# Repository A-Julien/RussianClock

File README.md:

# Projet Réveil Russe

## Présentation

Le réveil russe est une invention géniale de tube électronique pour un affichage 7 segments extremment classieux.

L'effet rendu est très geek vintage.

Nous avons l'objectif de créer une horloge à partir de ce type de tube, drivé astucieusement par un composant MAX et controllé en python par une carte Raspberry Pi 3.

## Développement

Nous allons développer le mappage des composants ainsi que le programme de controle du MAX en python.

## Documentation

Nous allons utiliser un certain nombre de documents, que nous poserons dans le dossier Documentation.

## Auteurs

Nous sommes étudiants en IUT d'informatique et à Polytech.

+	Julien Alaimo
+	Nans Faudon
+	Raphaël Castanier

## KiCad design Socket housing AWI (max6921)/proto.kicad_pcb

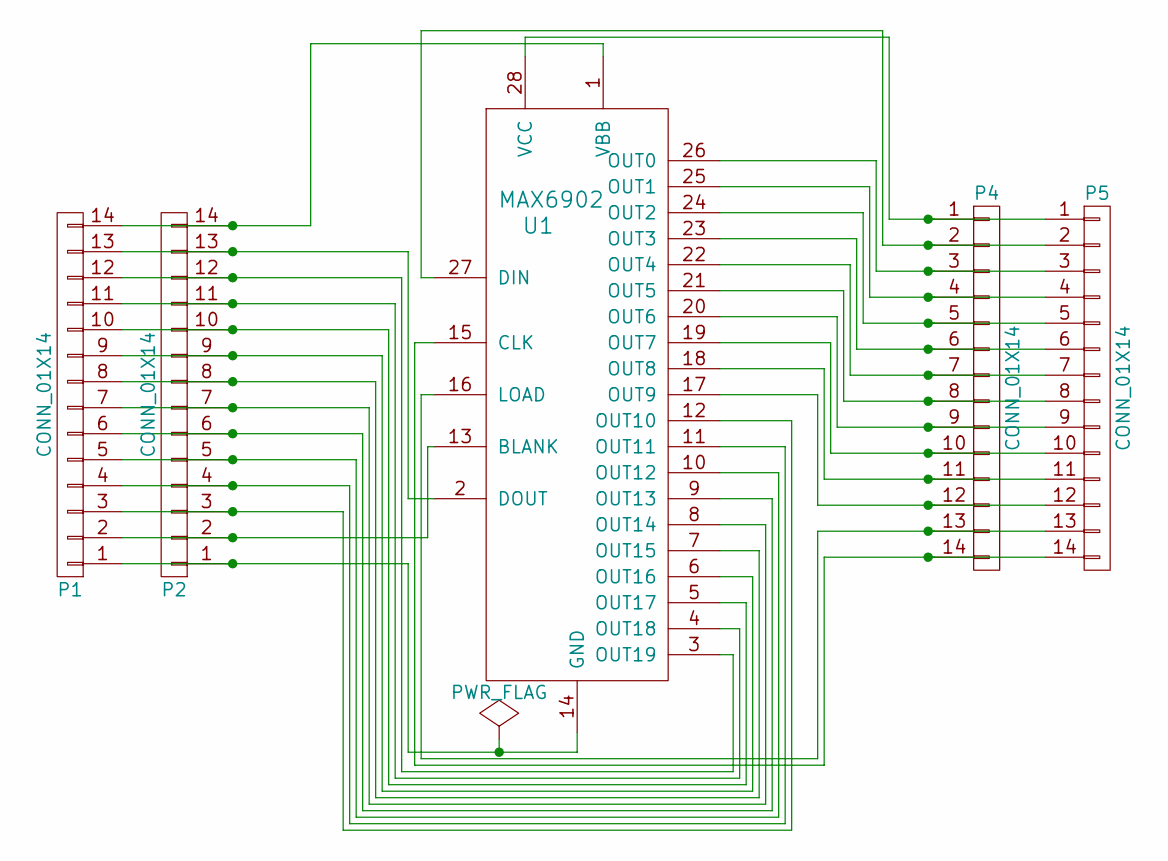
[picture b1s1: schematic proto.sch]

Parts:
P1, P2, P4, P5: CONN_01X14; Pin_Header_Straight_1x14_Pitch2.54mm
U1: MAX6902; MAX6921 - SOP28

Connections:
unnamed: P1.1, P2.1, U1.14 (GND)
unnamed: P1.2, P2.2, U1.13 (BLANK)
unnamed: P1.3, P2.3, U1.12 (OUT10)
unnamed: P1.4, P2.4, U1.11 (OUT11)
unnamed: P1.5, P2.5, U1.10 (OUT12)
unnamed: P1.6, P2.6, U1.9 (OUT13)
unnamed: P1.7, P2.7, U1.8 (OUT14)
unnamed: P1.8, P2.8, U1.7 (OUT15)
unnamed: P1.9, P2.9, U1.6 (OUT16)
unnamed: P1.10, P2.10, U1.5 (OUT17)
unnamed: P1.11, P2.11, U1.4 (OUT18)
unnamed: P1.12, P2.12, U1.3 (OUT19)
unnamed: P1.13, P2.13, U1.2 (DOUT)
unnamed: P1.14, P2.14, U1.1 (VBB)
unnamed: P4.1, P5.1, U1.28 (VCC)
unnamed: P4.2, P5.2, U1.27 (DIN)
unnamed: P4.3, P5.3, U1.26 (OUT0)
unnamed: P4.4, P5.4, U1.25 (OUT1)
unnamed: P4.5, P5.5, U1.24 (OUT2)
unnamed: P4.6, P5.6, U1.23 (OUT3)
unnamed: P4.7, P5.7, U1.22 (OUT4)
unnamed: P4.8, P5.8, U1.21 (OUT5)
unnamed: P4.9, P5.9, U1.20 (OUT6)
unnamed: P4.10, P5.10, U1.19 (OUT7)
unnamed: P4.11, P5.11, U1.18 (OUT8)
unnamed: P4.12, P5.12, U1.17 (OUT9)
unnamed: P4.13, P5.13, U1.16 (LOAD)
unnamed: P4.14, P5.14, U1.15 (CLK)

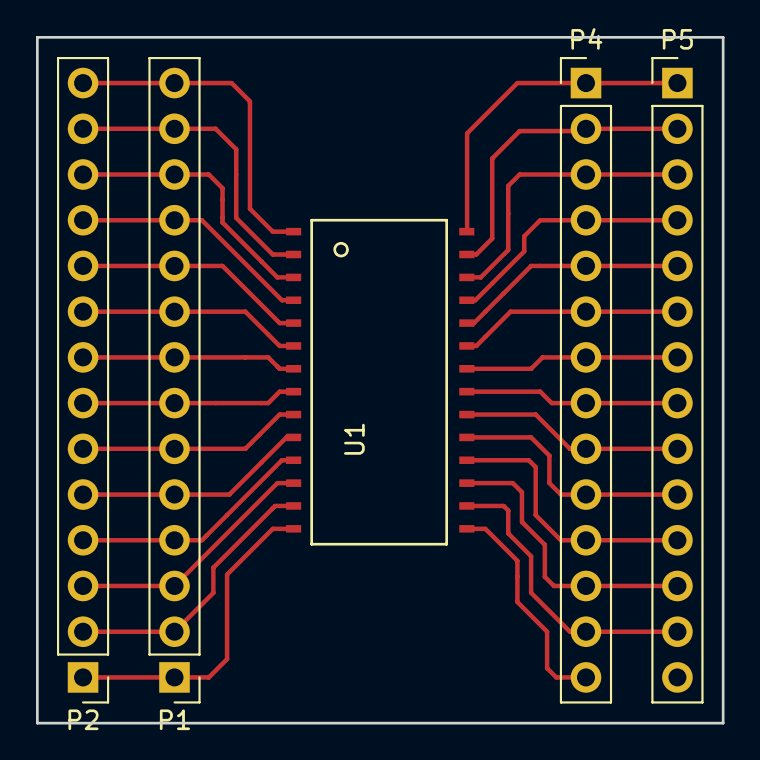
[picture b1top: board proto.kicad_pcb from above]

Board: 2 copper layers, 38.1 x 38.1 mm, 5 parts (0 on the bottom side), 28 nets.

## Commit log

2017-01-26 test de git
2017-01-26 Ajout de Coucou.md
2017-01-26 caonnard
2017-01-26 test mes couilles
2017-01-26 test encore
2017-01-26 Ajout des premiers srcipts python
2017-01-26 test commit branch
2017-01-26 bouffon
2017-01-26 supression de Coucou.md
2017-01-26 Change README.md
2017-01-26 Ajout de la doc du driver VFD
2017-01-26 Documentation
2017-01-26 Remove doc : creation d'un fichier dedié
2017-01-26 Ajout doc
2017-01-26 Rédaction de la présentation du README
2017-01-26 Mise à jour de la documentation
2017-02-05 ajout de la carte Socket pour le MAX6921 (CMS to Traversant)
2017-02-08 Ajout de fonctions de test pour le MAX
2017-03-12 Fix some GPIO problem, add a hello program
2017-03-13 Begin build of basic maxLib in python
2017-03-13 building maxLib in python [don't work]
